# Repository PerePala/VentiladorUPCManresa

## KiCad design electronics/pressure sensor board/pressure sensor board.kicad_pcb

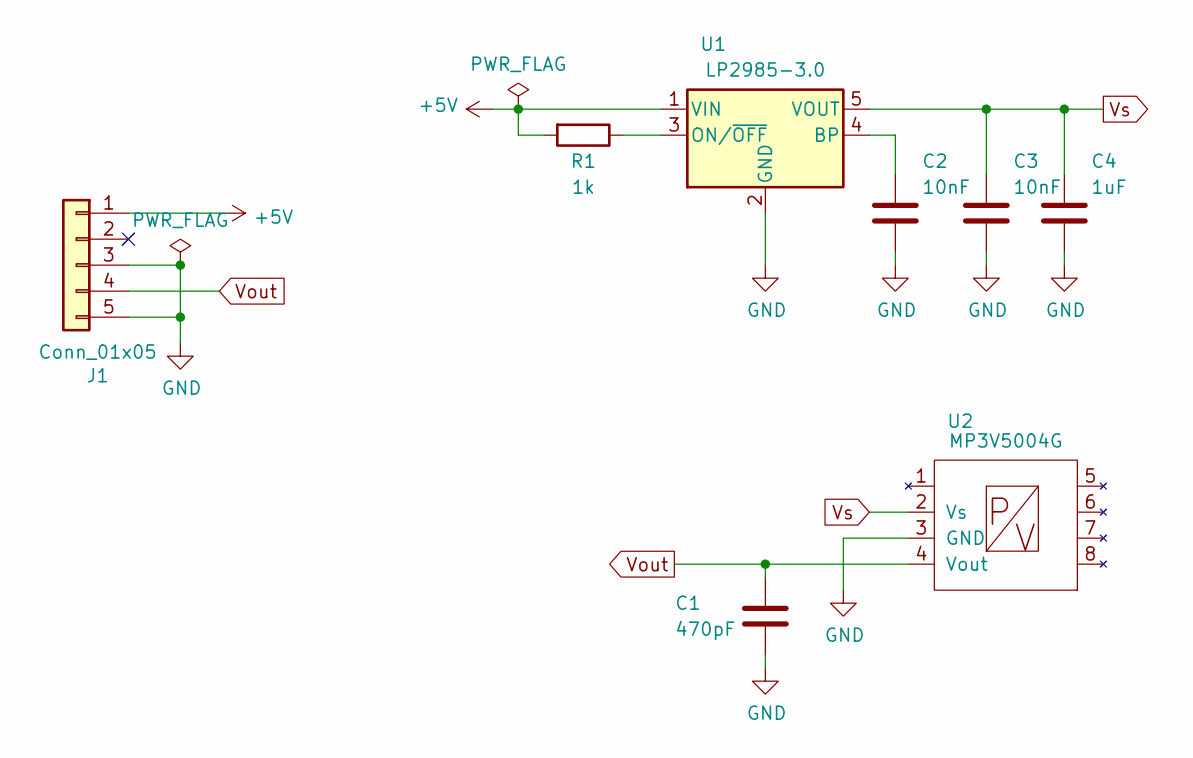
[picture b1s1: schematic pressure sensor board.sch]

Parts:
C1: 470pF; C_0805_2012Metric_Pad1.15x1.40mm_HandSolder
C2, C3: 10nF; C_0805_2012Metric_Pad1.15x1.40mm_HandSolder
C4: 1uF; C_0805_2012Metric_Pad1.15x1.40mm_HandSolder
J1: Conn_01x05; Molex_SL_171971-0005_1x05_P2.54mm_Vertical
R1: 1k; R_0805_2012Metric_Pad1.15x1.40mm_HandSolder
U1: LP2985-3.0; SOT-23-5
U2: MP3V5004G; MP3V5004

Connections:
+5V: J1.1, R1.2, U1.1 (VIN)
GND: C1.2, C2.2, C3.2, C4.2, J1.3, J1.5, U1.2 (GND), U2.3 (GND)
unnamed: C2.1, U1.4 (BP)
unnamed: R1.1, U1.3 (ON/~OFF~)
Vout: C1.1, J1.4, U2.4 (Vout)
Vs: C3.1, C4.1, U1.5 (VOUT), U2.2 (Vs)

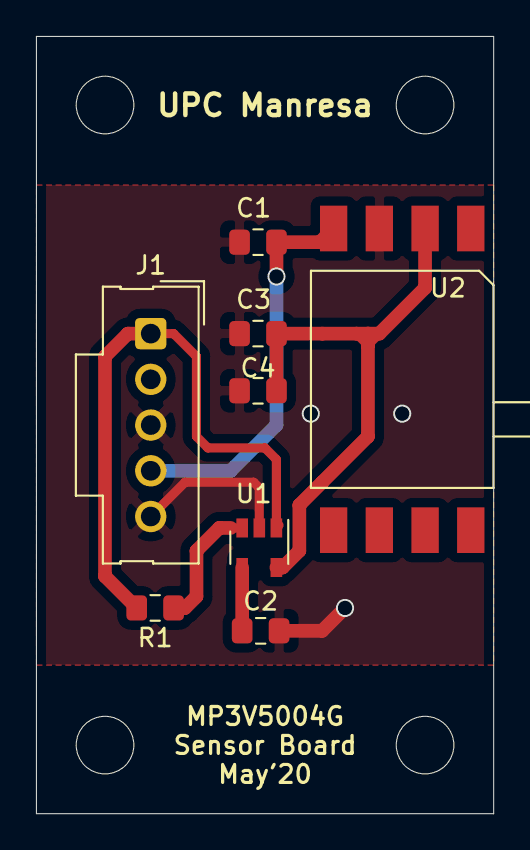
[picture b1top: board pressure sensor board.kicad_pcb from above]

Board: 2 copper layers, 25.4 x 43.2 mm, 8 parts (0 on the bottom side), 6 nets.

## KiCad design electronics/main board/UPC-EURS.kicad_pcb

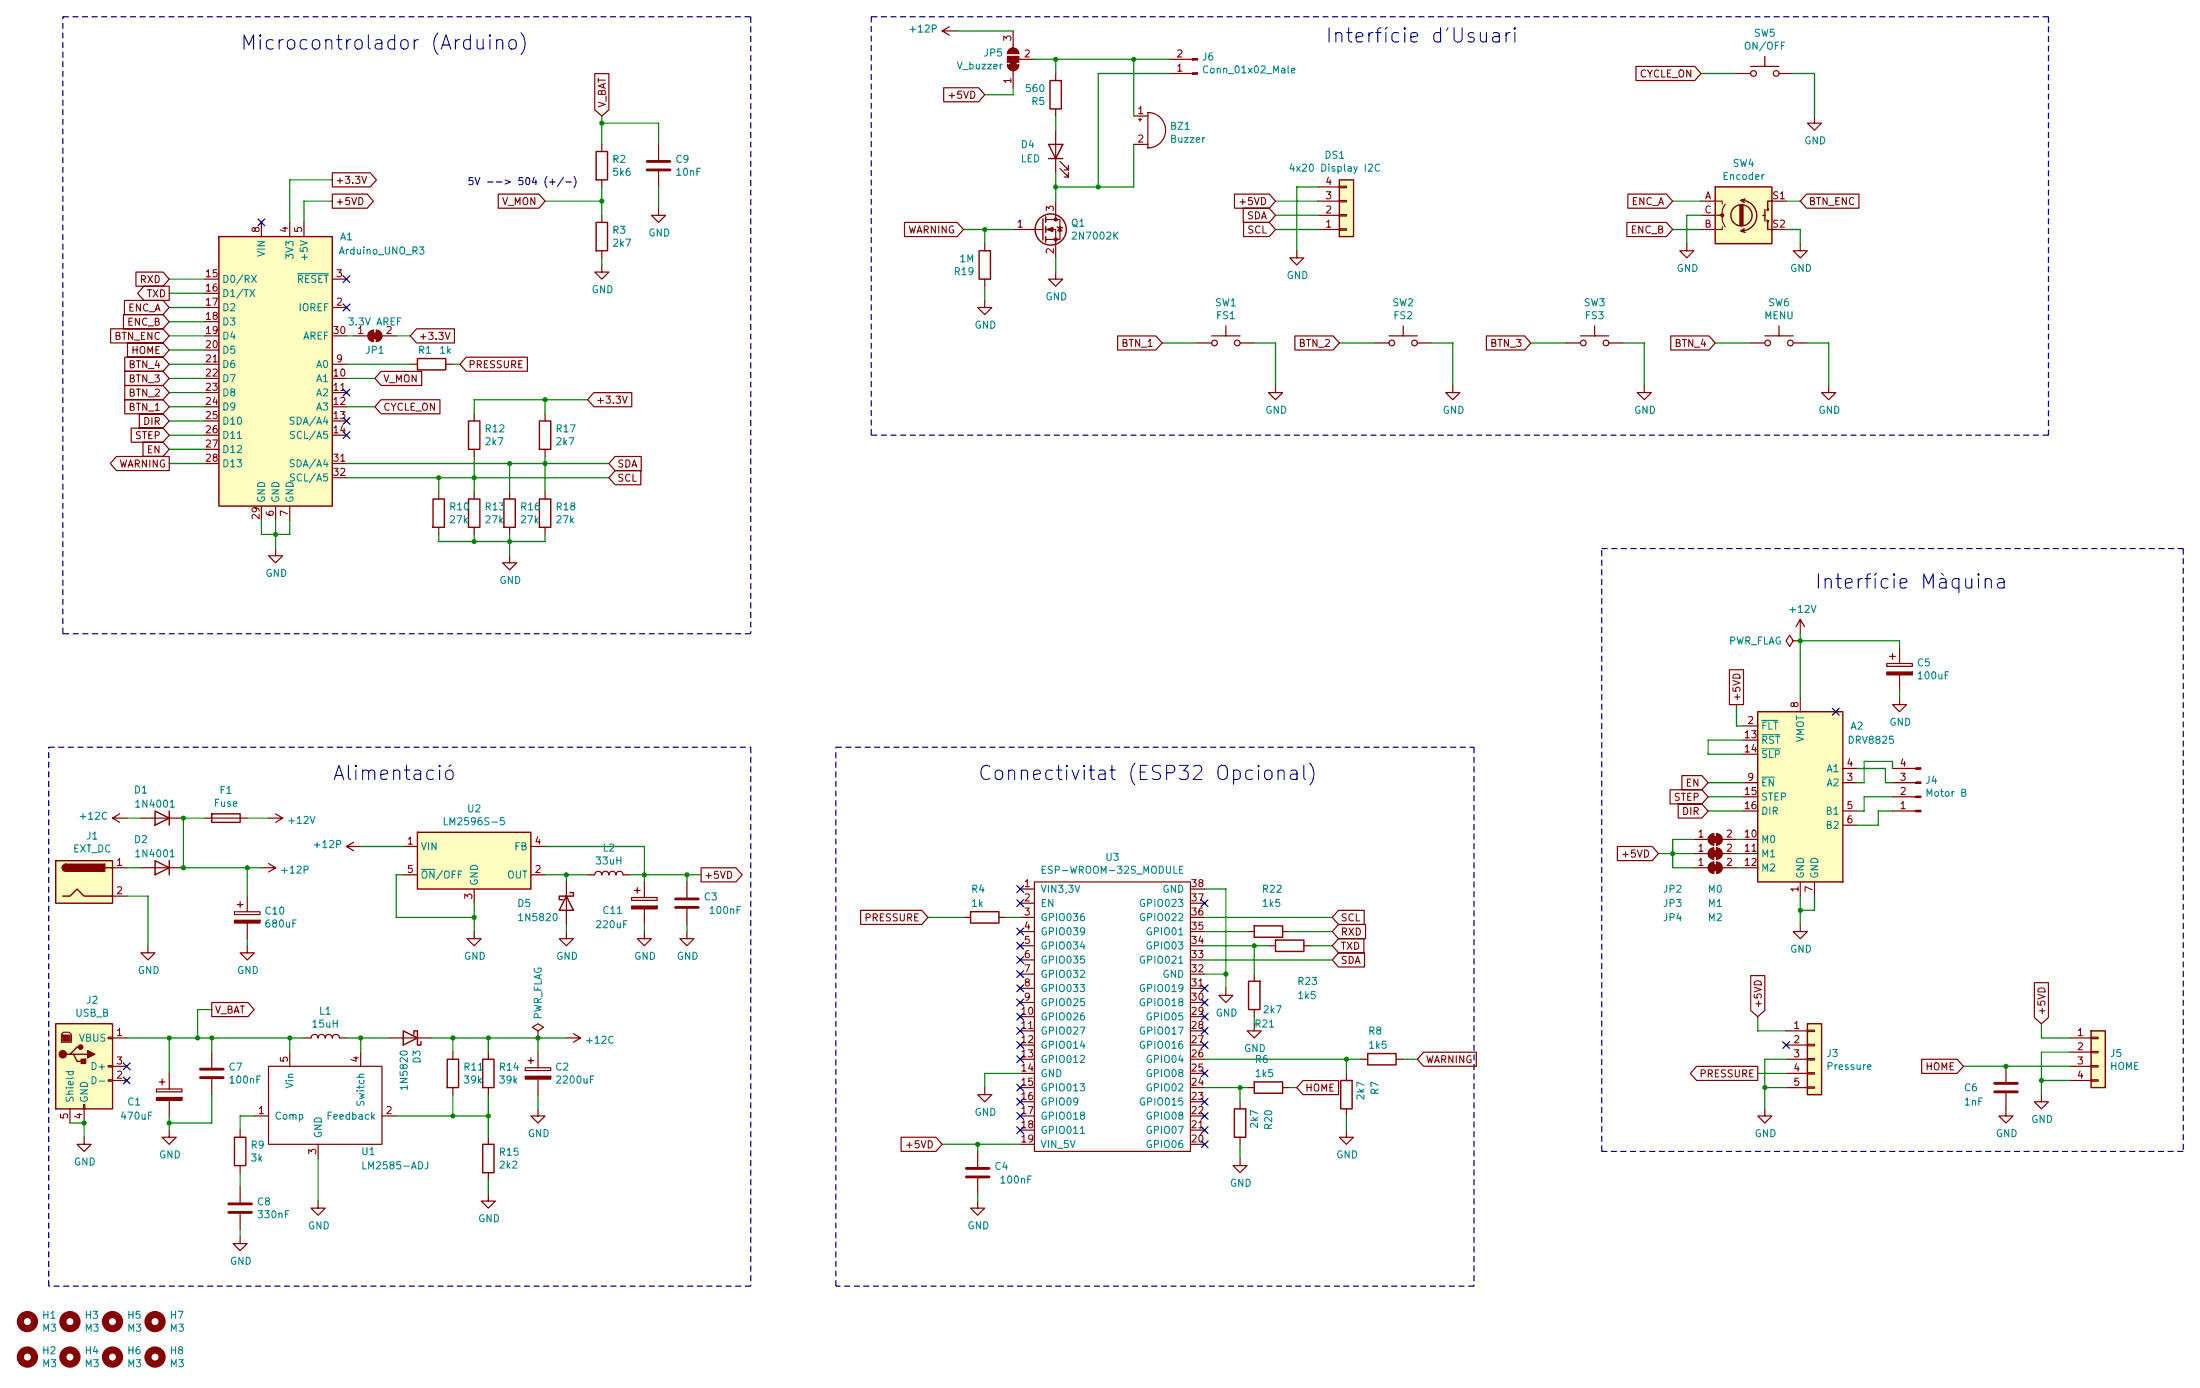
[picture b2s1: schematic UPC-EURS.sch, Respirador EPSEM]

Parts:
A1: Arduino_UNO_R3
A2: DRV8825; Pololu_Breakout-16_15.2x20.3mm
BZ1: Buzzer; Buzzer_12x9.5RM7.6
C1: 470uF; CP_Radial_D8.0mm_P3.50mm
C2: 2200uF; CP_Radial_D16.0mm_P7.50mm
C3, C4, C7: 100nF; C_0805_2012Metric_Pad1.15x1.40mm_HandSolder
C5: 100uF; CP_Radial_D8.0mm_P3.50mm
C6: 1nF; C_0805_2012Metric_Pad1.15x1.40mm_HandSolder
C8: 330nF; C_0805_2012Metric_Pad1.15x1.40mm_HandSolder
C9: 10nF; C_0805_2012Metric_Pad1.15x1.40mm_HandSolder
C10: 680uF; CP_Radial_D12.5mm_P5.00mm
C11: 220uF; CP_Radial_D8.0mm_P3.50mm
D1, D2: 1N4001; D_DO-41_SOD81_P10.16mm_Horizontal
D3, D5: 1N5820; D_DO-201AD_P15.24mm_Horizontal
D4: LED; LED_D5.0mm
DS1: 4x20 Display I2C; PinSocket_1x04_P2.54mm_Horizontal
F1: Fuse; Radial_Lead_Micro_Fuse
H1, H2, H3, H4, H5, H6, H7, H8: M3; MountingHole_3.2mm_M3
J1: EXT_DC; BarrelJack_Horizontal
J2: USB_B; USB_B_OST_USB-B1HSxx_Horizontal
J3: Pressure; Molex_SL_171971-0005_1x05_P2.54mm_Vertical
J4: Motor B; TerminalBlock_bornier-4_P5.08mm
J5: HOME; Molex_SL_171971-0004_1x04_P2.54mm_Vertical
J6: Conn_01x02_Male; PinHeader_1x02_P2.54mm_Vertical
JP1: 3.3V AREF; SolderJumper-2_P1.3mm_Bridged_Pad1.0x1.5mm
JP2: M0; SolderJumper-2_P1.3mm_Bridged_Pad1.0x1.5mm
JP3: M1; SolderJumper-2_P1.3mm_Bridged_Pad1.0x1.5mm
JP4: M2; SolderJumper-2_P1.3mm_Bridged_Pad1.0x1.5mm
JP5: V_buzzer; SolderJumper-3_P1.3mm_Bridged12_RoundedPad1.0x1.5mm
L1: 15uH; L_Radial_D8.7mm_P5.00mm_Fastron_07HCP
L2: 33uH; L_Radial_D8.7mm_P5.00mm_Fastron_07HCP
Q1: 2N7002K; SOT-23
R1, R4: 1k; R_0805_2012Metric_Pad1.15x1.40mm_HandSolder
R2: 5k6; R_0805_2012Metric_Pad1.15x1.40mm_HandSolder
R3, R7, R12, R17, R20, R21: 2k7; R_0805_2012Metric_Pad1.15x1.40mm_HandSolder
R5: 560; R_0805_2012Metric_Pad1.15x1.40mm_HandSolder
R6, R8, R22, R23: 1k5; R_0805_2012Metric_Pad1.15x1.40mm_HandSolder
R9: 3k; R_0805_2012Metric_Pad1.15x1.40mm_HandSolder
R10, R13, R16, R18: 27k; R_0805_2012Metric_Pad1.15x1.40mm_HandSolder
R11, R14: 39k; R_0805_2012Metric_Pad1.15x1.40mm_HandSolder
R15: 2k2; R_0805_2012Metric_Pad1.15x1.40mm_HandSolder
R19: 1M; R_0805_2012Metric_Pad1.15x1.40mm_HandSolder
SW1: FS1; SW_PUSH_6mm_H13mm
SW2: FS2; SW_PUSH_6mm_H13mm
SW3: FS3; SW_PUSH_6mm_H13mm
SW4: Encoder; RotaryEncoder_Alps_EC12E-Switch_Vertical_H20mm_CircularMoun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
SW5: ON/OFF; SW_PUSH_6mm_H13mm
SW6: MENU; SW_PUSH_6mm_H13mm
U1: LM2585-ADJ; TO-263-5_TabPin6
U2: LM2596S-5; TO-263-5_TabPin3
U3: ESP-WROOM-32S_MODULE; ESP32_MODULE

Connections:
+3.3V: A1.4 (3V3), JP1.2 (B), R12.1, R17.1
+5VD: A1.5 (+5V), A2.2 (~FLT), C3.1, C4.1, C11.1, DS1.3, J3.1, J5.1, JP2.1 (A), JP3.1 (A), JP4.1 (A), JP5.1 (A), L2.2, U2.4 (FB), U3.19 (VIN_5V)
+12C: C2.1, D1.2 (A), D3.1 (K), R11.1, R14.1
+12P: C10.1, D1.1 (K), D2.1 (K), F1.2, JP5.3 (B), U2.1 (VIN)
+12V: A2.8 (VMOT), C5.1, F1.1
BTN_1: A1.24 (D9), SW1.1
BTN_2: A1.23 (D8), SW2.1
BTN_3: A1.22 (D7), SW3.1
BTN_4: A1.21 (D6), SW6.1
BTN_ENC: A1.19 (D4), SW4.S1
CYCLE_ON: A1.12 (A3), SW5.1
DIR: A1.25 (D10), A2.16 (DIR)
EN: A1.27 (D12), A2.9 (~EN)
ENC_A: A1.17 (D2), SW4.A
ENC_B: A1.18 (D3), SW4.B
GND: A1.6 (GND), A1.7 (GND), A1.29 (GND), A2.1 (GND), A2.7 (GND), C1.2, C2.2, C3.2, C4.2, C5.2, C6.2, C7.2, C8.2, C9.2, C10.2, C11.2, D5.2 (A), DS1.4, J1.2, J1.3, J2.4 (GND), J2.5 (Shield), J3.3, J3.5, J5.2, J5.4, Q1.2 (S), R3.2, R7.1, R10.2, R13.2, R15.2, R16.2, R18.2, R19.1, R20.1, R21.1, SW1.2, SW2.2, SW3.2, SW4.C, SW4.MP, SW4.S2, SW5.2, SW6.2, U1.3 (GND), U2.3 (GND), U2.5 (~ON~/OFF), U3.14 (GND), U3.32 (GND), U3.38 (GND)
HOME: A1.20 (D5), C6.1, J5.3, R6.1
unnamed: A1.9 (A0), R1.2
unnamed: A1.30 (AREF), JP1.1 (A)
unnamed: A2.3 (A2), J4.4
unnamed: A2.4 (A1), J4.3
unnamed: A2.5 (B1), J4.2
unnamed: A2.6 (B2), J4.1
unnamed: A2.10 (M0), JP2.2 (B)
unnamed: A2.11 (M1), JP3.2 (B)
unnamed: A2.12 (M2), JP4.2 (B)
unnamed: A2.13 (~RST), A2.14 (~SLP)
unnamed: BZ1.1 (-), J6.2, JP5.2 (C), R5.2
unnamed: BZ1.2 (+), D4.1 (K), J6.1, Q1.3 (D)
unnamed: C8.1, R9.2
unnamed: D2.2 (A), J1.1
unnamed: D3.2 (A), L1.2, U1.4 (Switch)
unnamed: D4.2 (A), R5.1
unnamed: D5.1 (K), L2.1, U2.2 (OUT)
unnamed: R4.1, U3.3 (GPIO036)
unnamed: R7.2, R8.2, U3.26 (GPIO04)
unnamed: R9.1, U1.1 (Comp)
unnamed: R11.2, R14.2, R15.1, U1.2 (Feedback)
unnamed: R6.2, R20.2, U3.24 (GPIO02)
unnamed: R21.2, R23.2, U3.34 (GPIO03)
unnamed: R22.2, U3.35 (GPIO01)
PRESSURE: J3.4, R1.1, R4.2
RXD: A1.15 (D0/RX), R22.1
SCL: A1.32 (SCL/A5), DS1.1, R10.1, R12.2, R13.1, U3.36 (GPIO022)
SDA: A1.31 (SDA/A4), DS1.2, R16.1, R17.2, R18.1, U3.33 (GPIO021)
STEP: A1.26 (D11), A2.15 (STEP)
TXD: A1.16 (D1/TX), R23.1
V_BAT: C1.1, C7.1, C9.1, J2.1 (VBUS), L1.1, R2.1, U1.5 (Vin)
V_MON: A1.10 (A1), R2.2, R3.1
WARNING: A1.28 (D13), Q1.1 (G), R8.1, R19.2

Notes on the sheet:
5V --> 504 (+/-)
Interfície d'Usuari
Microcontrolador (Arduino)
Alimentació
Connectivitat (ESP32 Opcional)
Interfície Màquina

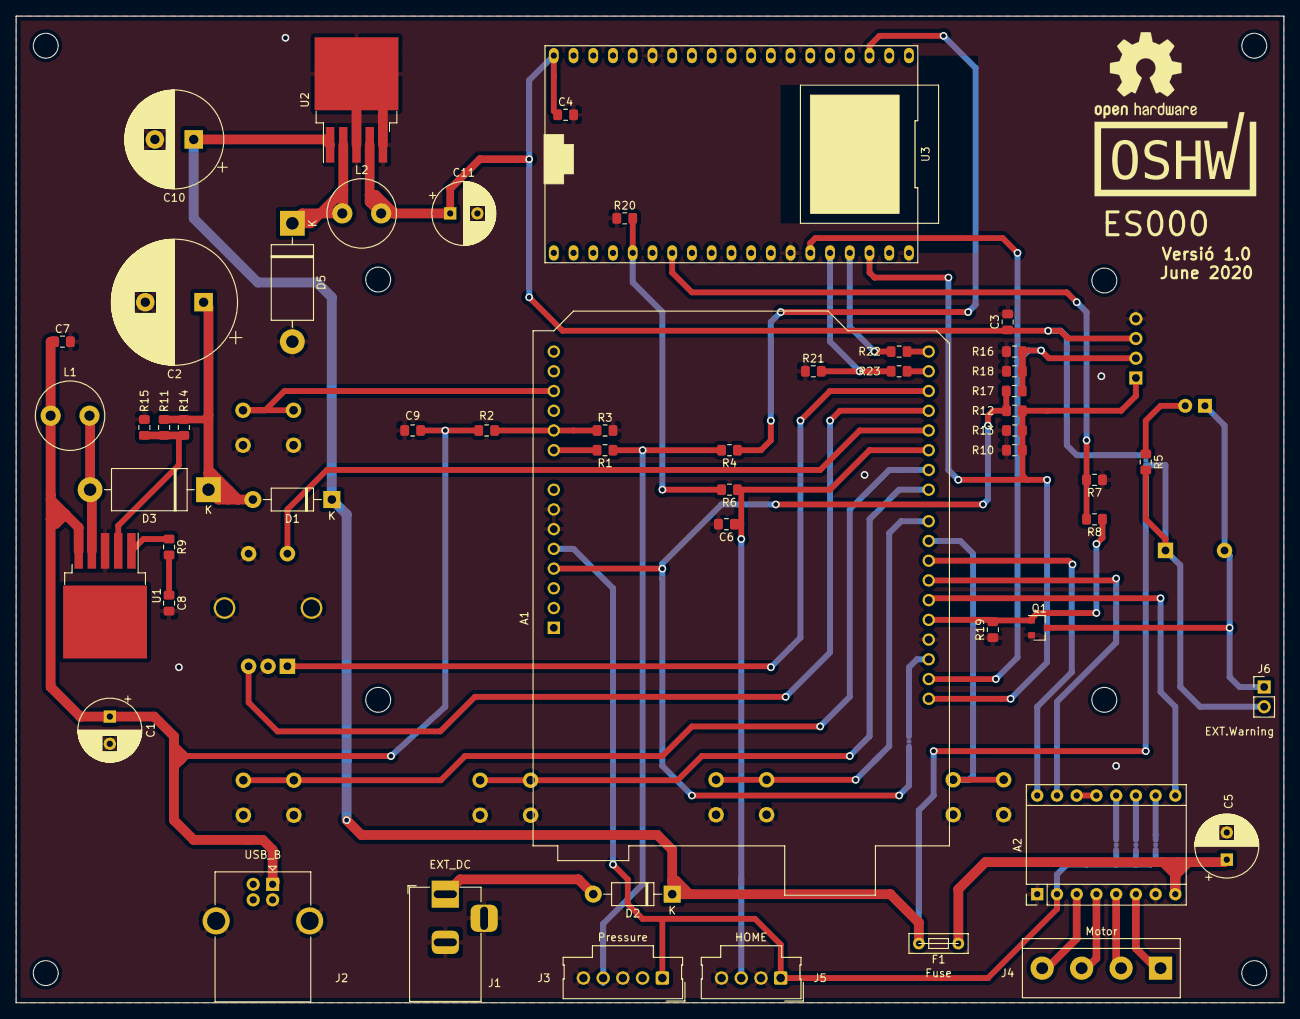
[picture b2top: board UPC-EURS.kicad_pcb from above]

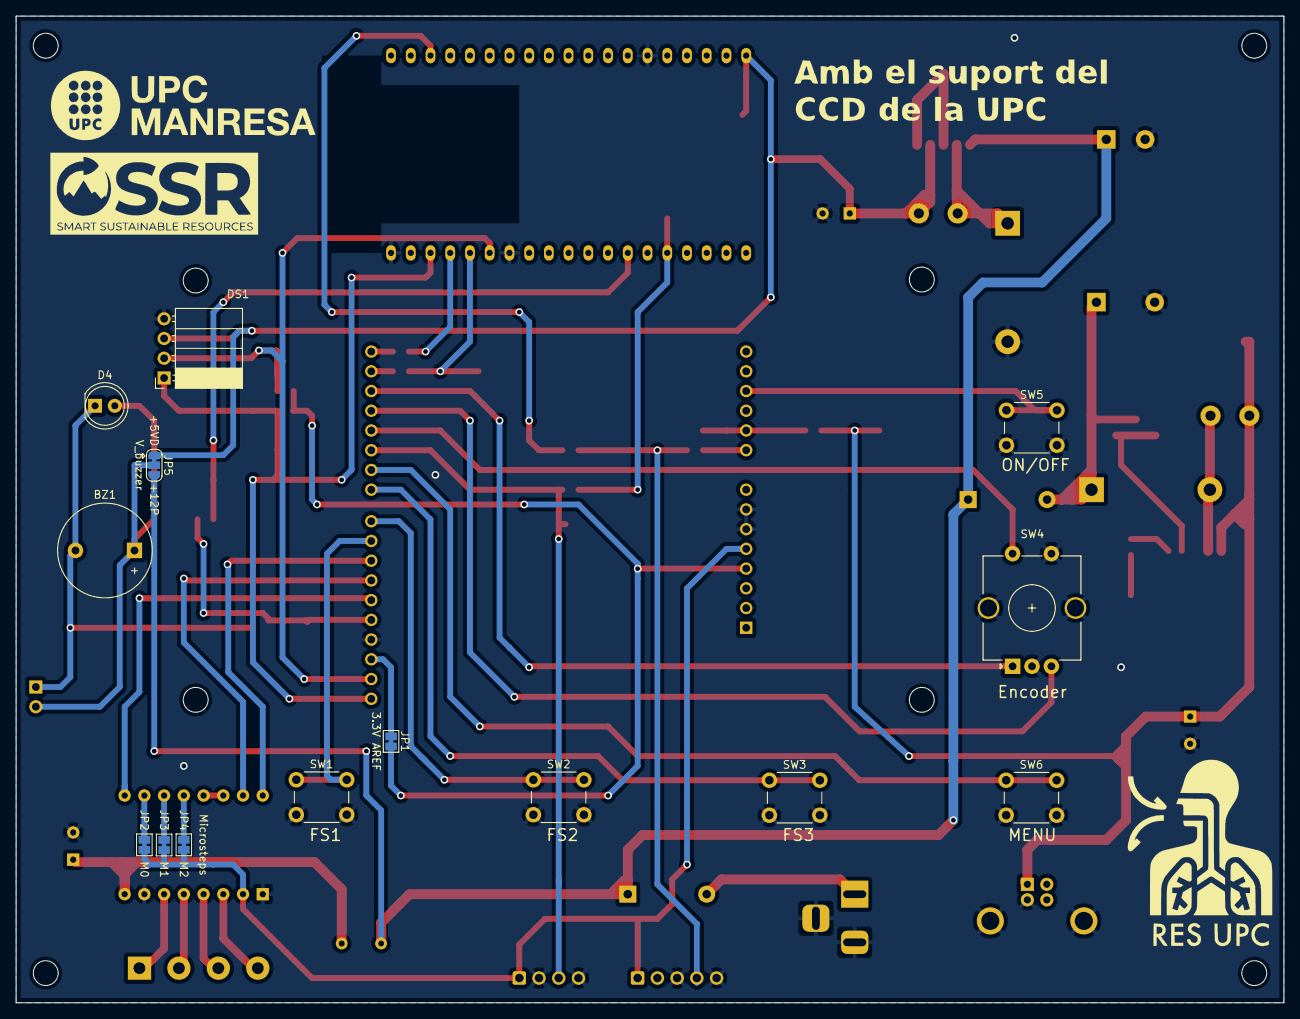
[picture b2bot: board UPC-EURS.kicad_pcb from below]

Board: 2 copper layers, 163.2 x 127.0 mm, 76 parts (14 on the bottom side), 50 nets.

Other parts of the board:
OSHW_Mono_0.5_Scale: ES000; OSHW_Mono_0.5_Scale

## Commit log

2020-07-06 Afegit nou directori de hardware electronic
2020-12-05 Last developments on the display modules
2020-12-08 Implemented the I2C display and the main UI functions.
2020-12-11 Implemented min/max values
2020-12-13 Save new value implemented. Form and field refactoring.
2020-12-16 UI module added to main and connected to vaction
2020-12-16 Motor pins changed according to the schematics
2020-12-17 Changed ENABLE motor's logic (LOW = Enabled)
2020-12-18 Add switch.c to UI. Add start/stop to vaction
2020-12-18 Add value to Ventilator. Avoid non-initialized value
2020-12-18 Modules changed by switch module
2020-12-18 #include "button.h" not needed anymore
2020-12-23 Implemented macro to simplify the code
